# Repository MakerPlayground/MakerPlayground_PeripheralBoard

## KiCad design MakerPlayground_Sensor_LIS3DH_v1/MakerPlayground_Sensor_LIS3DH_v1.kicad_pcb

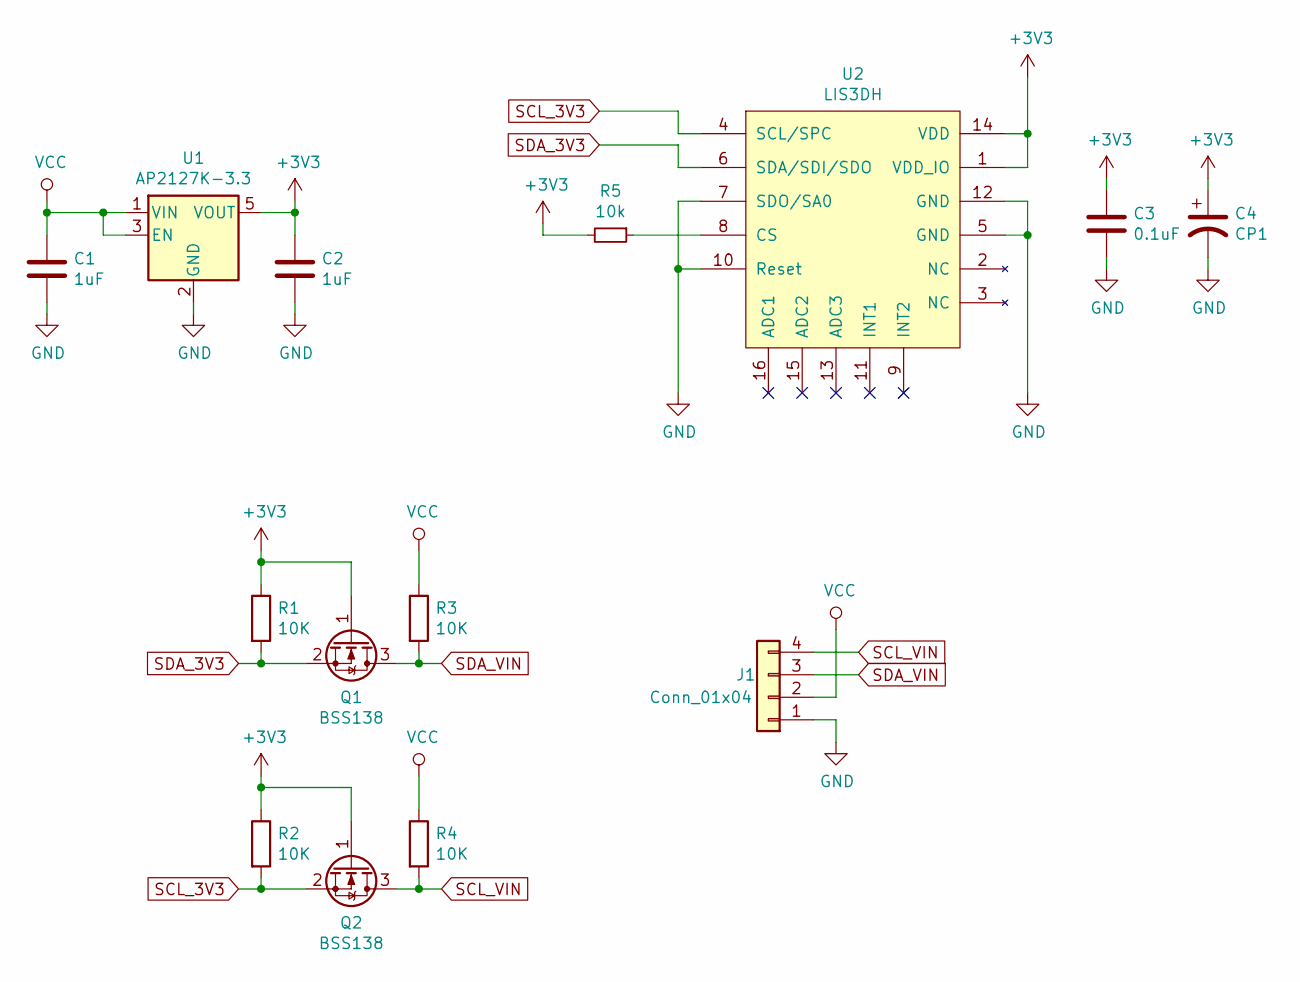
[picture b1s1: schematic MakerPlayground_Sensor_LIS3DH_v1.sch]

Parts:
C1, C2: 1uF; C_0603_1608Metric
C3: 0.1uF; C_0603_1608Metric
C4: CP1; CP_EIA-3216-12_Kemet-S
J1: Conn_01x04; JST_PH_S4B-PH-SM4-TB_1x04-1MP_P2.00mm_Horizontal
Q1, Q2: BSS138; SOT-23
R1, R2, R3, R4: 10K; R_0603_1608Metric
R5: 10k; R_0603_1608Metric
U1: AP2127K-3.3; SOT-23-5
U2: LIS3DH

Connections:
+3V3: C2.1, C3.1, C4.1, Q1.1 (G), Q2.1 (G), R1.1, R2.1, R5.2, U1.5 (VOUT), U2.1 (VDD_IO), U2.14 (VDD)
GND: C1.2, C2.2, C3.2, C4.2, J1.1, U1.2 (GND), U2.5 (GND), U2.7 (SDO/SA0), U2.10 (Reset), U2.12 (GND)
unnamed: R5.1, U2.8 (CS)
SCL_3V3: Q2.2 (S), R2.2, U2.4 (SCL/SPC)
SCL_VIN: J1.4, Q2.3 (D), R4.2
SDA_3V3: Q1.2 (S), R1.2, U2.6 (SDA/SDI/SDO)
SDA_VIN: J1.3, Q1.3 (D), R3.2
VCC: C1.1, J1.2, R3.1, R4.1, U1.1 (VIN), U1.3 (EN)

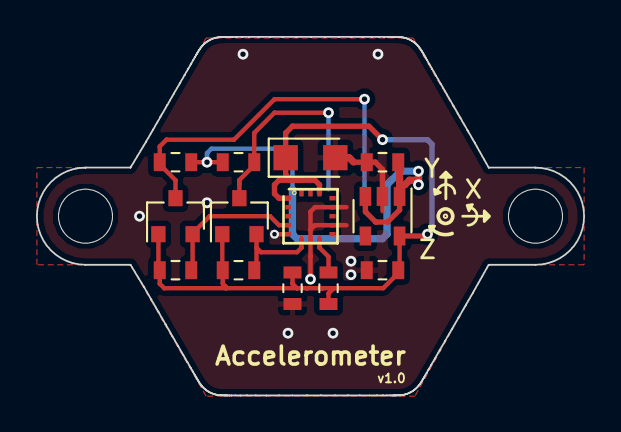
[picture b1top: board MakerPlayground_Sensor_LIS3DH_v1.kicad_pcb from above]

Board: 2 copper layers, 30.4 x 19.9 mm, 14 parts (1 on the bottom side), 8 nets.

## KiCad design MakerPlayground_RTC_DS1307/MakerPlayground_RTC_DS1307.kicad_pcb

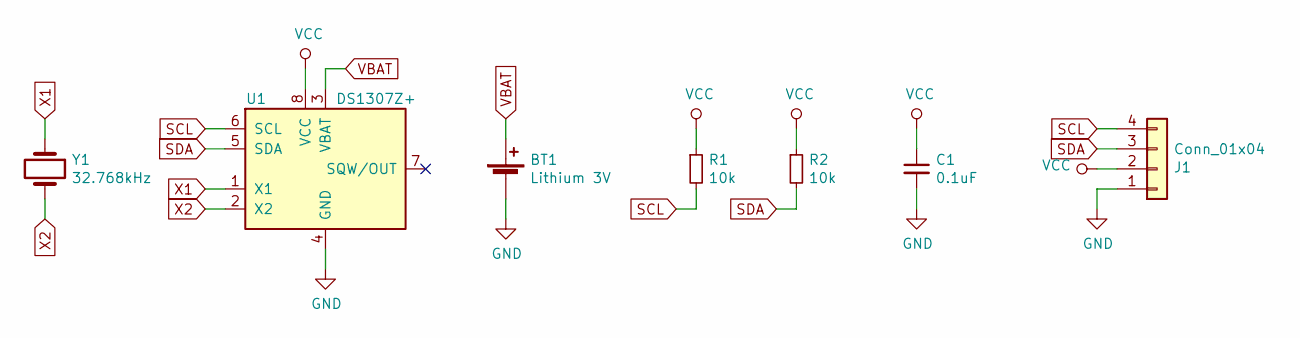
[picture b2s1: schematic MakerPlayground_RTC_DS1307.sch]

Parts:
BT1: Lithium 3V; BL-25T-GLT
C1: 0.1uF; C_0603_1608Metric
J1: Conn_01x04; JST_PH_S4B-PH-K_1x04_P2.00mm_Horizontal
R1, R2: 10k; R_0603_1608Metric
U1: DS1307Z+; SOIC-8_3.9x4.9mm_P1.27mm
Y1: 32.768kHz; Crystal_SMD_3215-2Pin_3.2x1.5mm

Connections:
GND: BT1.2 (-), C1.2, J1.1, U1.4 (GND)
SCL: J1.4, R1.2, U1.6 (SCL)
SDA: J1.3, R2.2, U1.5 (SDA)
VBAT: BT1.1 (+), U1.3 (VBAT)
VCC: C1.1, J1.2, R1.1, R2.1, U1.8 (VCC)
X1: U1.1 (X1), Y1.1
X2: U1.2 (X2), Y1.2

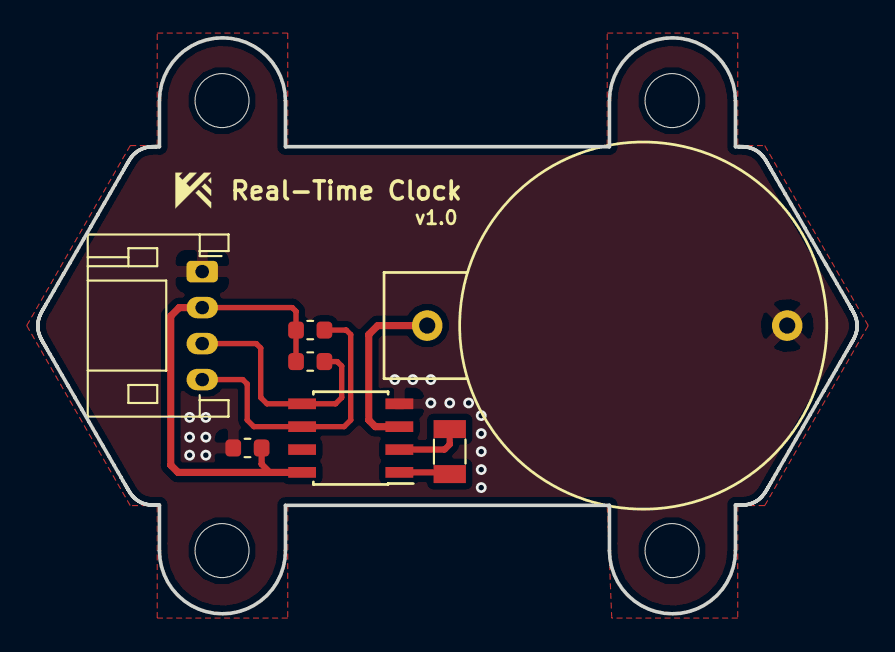
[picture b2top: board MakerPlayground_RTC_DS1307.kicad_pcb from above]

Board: 2 copper layers, 45.5 x 32.0 mm, 7 parts (0 on the bottom side), 7 nets.

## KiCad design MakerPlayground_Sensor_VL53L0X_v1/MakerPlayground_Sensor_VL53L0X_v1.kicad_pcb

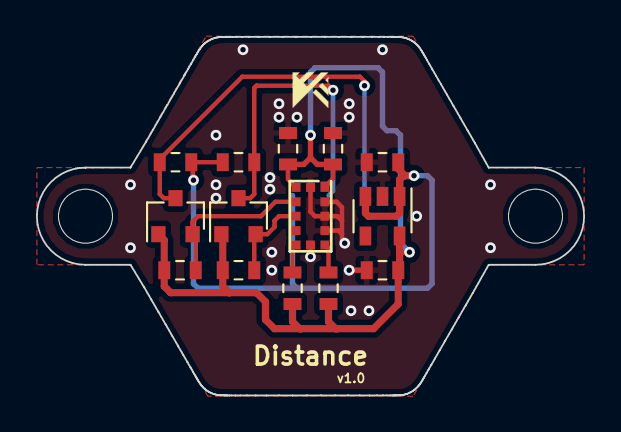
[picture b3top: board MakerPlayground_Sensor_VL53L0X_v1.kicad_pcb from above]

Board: 2 copper layers, 30.4 x 19.9 mm, 15 parts (1 on the bottom side), 9 nets.

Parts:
C1: 4.7uF; C_0603_1608Metric
C2: 0.1uF; C_0603_1608Metric
C4, C5: 1uF; C_0603_1608Metric
J1: Connector; JST_PH_S4B-PH-SM4-TB_1x04-1MP_P2.00mm_Horizontal
Q1, Q2: BSS138; SOT-23
R1, R2, R3, R4, R5, R6: 10k; R_0603_1608Metric
U1: VL53L0X
U2: AP2127K-3.3; SOT-23-5

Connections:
+3V3: C1.1, C2.1, C5.1, Q1.1, Q2.1, R1.1, R3.2, R5.2, R6.1, U1.1, U1.11, U2.5
GND: C1.2, C2.2, C4.2, C5.2, J1.1, U1.2, U1.3, U1.4, U1.6, U1.12, U2.2
unnamed: R1.2, U1.7
unnamed: R6.2, U1.5
SCL: J1.4, Q2.3, R4.1
SCL_S: Q2.2, R5.1, U1.10
SDA: J1.3, Q1.3, R2.1
SDA_S: Q1.2, R3.1, U1.9
VCC: C4.1, J1.2, R2.2, R4.2, U2.1, U2.3

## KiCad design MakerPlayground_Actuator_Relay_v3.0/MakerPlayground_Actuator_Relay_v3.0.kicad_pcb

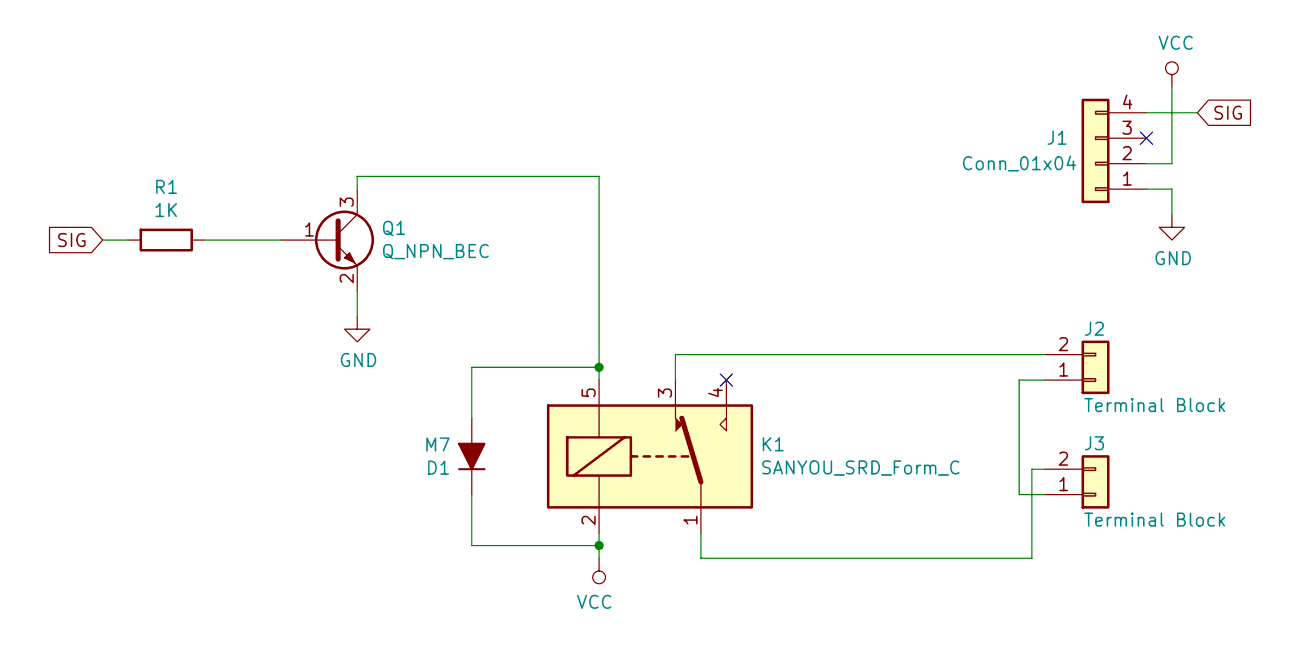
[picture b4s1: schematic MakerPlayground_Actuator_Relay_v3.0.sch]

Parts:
D1: M7; D_SMA
J1: Conn_01x04; JST_PH_S4B-PH-K_1x04_P2.00mm_Horizontal
J2, J3: Terminal Block; TerminalBlock_Dinkle_ED350V_1x02_P3.50mm_Horizontal
K1: SANYOU_SRD_Form_C; Relay_SPDT_SANYOU_SRD_Series_Form_C
Q1: Q_NPN_BEC; SOT-23
R1: 1K; R_0603_1608Metric

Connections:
GND: J1.1, Q1.2 (E)
unnamed: D1.2 (A), K1.5, Q1.3 (C)
unnamed: J2.1, J3.1
unnamed: J2.2, K1.3
unnamed: J3.2, K1.1
unnamed: Q1.1 (B), R1.1
SIG: J1.4, R1.2
VCC: D1.1 (K), J1.2, K1.2

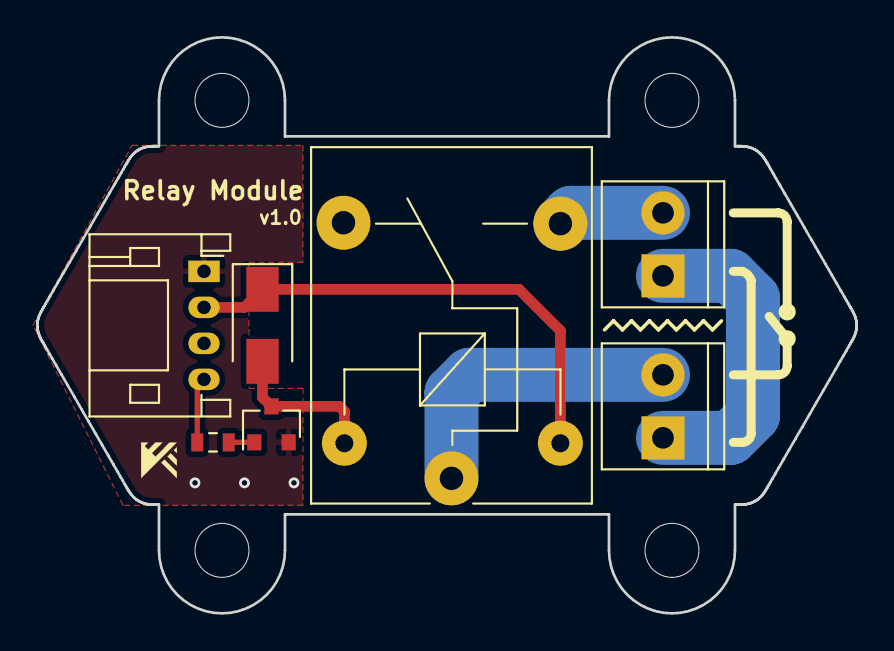
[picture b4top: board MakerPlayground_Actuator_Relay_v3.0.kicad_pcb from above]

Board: 2 copper layers, 45.5 x 32.0 mm, 7 parts (0 on the bottom side), 8 nets.

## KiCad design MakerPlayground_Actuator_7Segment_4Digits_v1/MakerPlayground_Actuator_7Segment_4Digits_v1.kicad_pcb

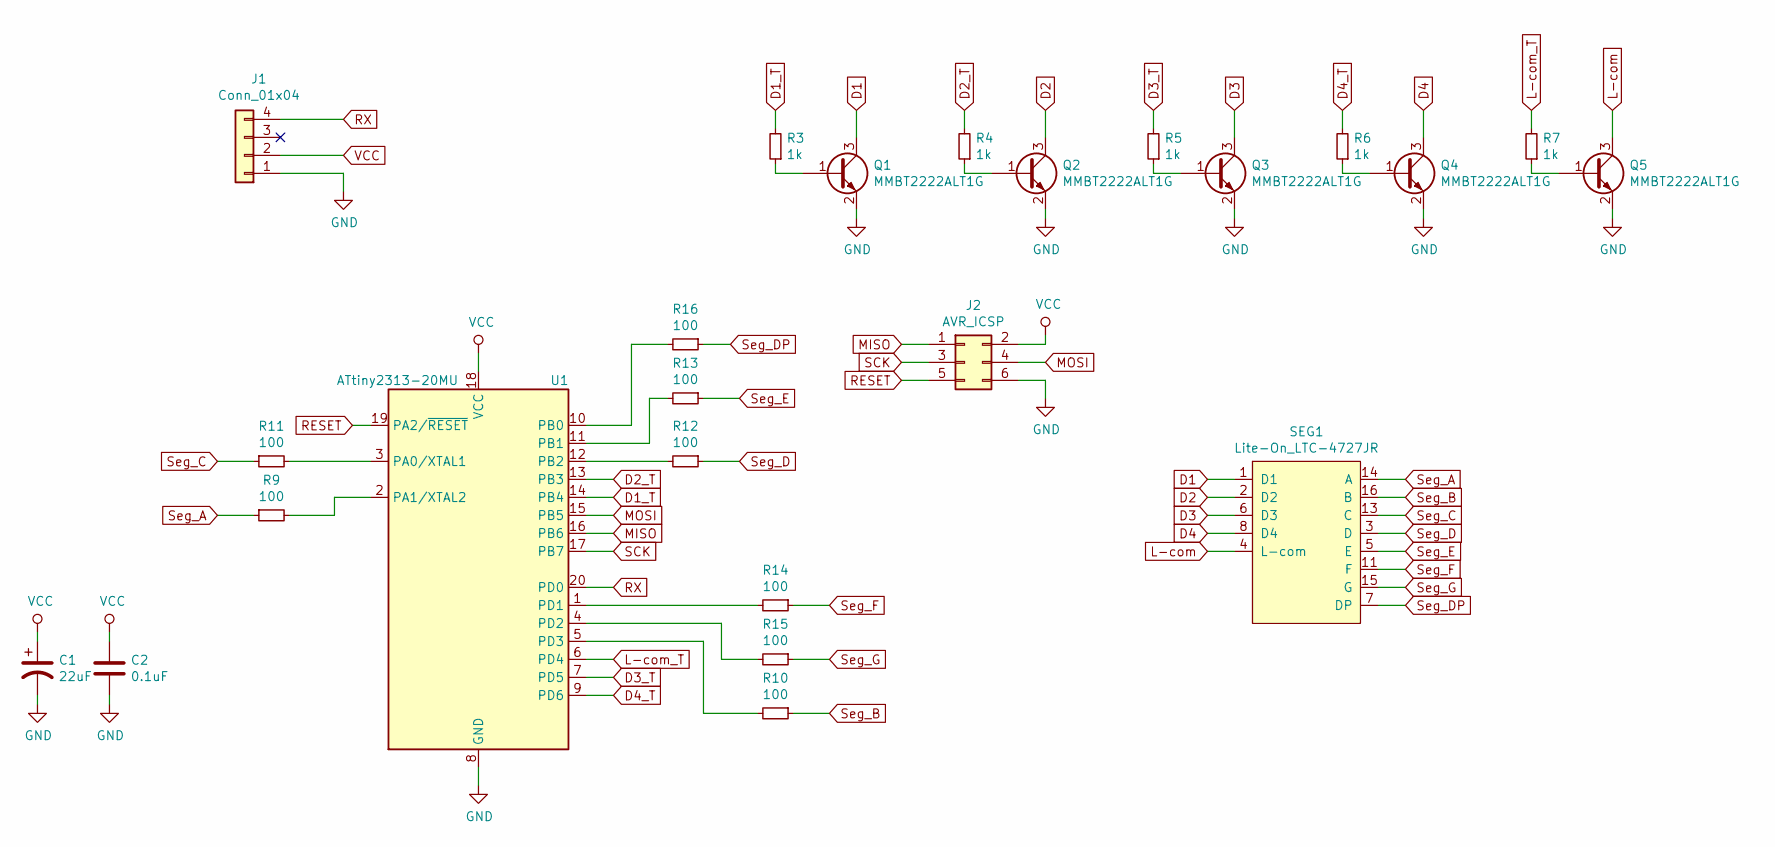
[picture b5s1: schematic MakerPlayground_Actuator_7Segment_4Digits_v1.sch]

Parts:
C1: 22uF; CP_EIA-3216-12_Kemet-S
C2: 0.1uF; C_0603_1608Metric
J1: Conn_01x04; JST_PH_S4B-PH-SM4-TB_1x04-1MP_P2.00mm_Horizontal
J2: AVR_ICSP; PinHeader_2x03_P2.54mm_Vertical
Q1, Q2, Q3, Q4, Q5: MMBT2222ALT1G; SOT-23
R3, R4, R5, R6, R7: 1k; R_0603_1608Metric
R9, R10, R11, R12, R13, R14, R15, R16: 100; R_0603_1608Metric
SEG1: Lite-On_LTC-4727JR; LTC-4727JR
U1: ATtiny2313-20MU; QFN-20-1EP_4x4mm_P0.5mm_EP2.5x2.5mm

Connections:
D1: Q1.3 (C), SEG1.1 (D1)
D1_T: R3.2, U1.14 (PB4)
D2: Q2.3 (C), SEG1.2 (D2)
D2_T: R4.2, U1.13 (PB3)
D3: Q3.3 (C), SEG1.6 (D3)
D3_T: R5.2, U1.7 (PD5)
D4: Q4.3 (C), SEG1.8 (D4)
D4_T: R6.2, U1.9 (PD6)
GND: C1.2, C2.2, J1.1, J2.6, Q1.2 (E), Q2.2 (E), Q3.2 (E), Q4.2 (E), Q5.2 (E), U1.8 (GND), U1.21 (GND)
L-com: Q5.3 (C), SEG1.4 (L-com)
L-com_T: R7.2, U1.6 (PD4)
MISO: J2.1, U1.16 (PB6)
MOSI: J2.4, U1.15 (PB5)
unnamed: Q1.1 (B), R3.1
unnamed: Q2.1 (B), R4.1
unnamed: Q3.1 (B), R5.1
unnamed: Q4.1 (B), R6.1
unnamed: Q5.1 (B), R7.1
unnamed: R9.2, U1.2 (PA1/XTAL2)
unnamed: R10.2, U1.5 (PD3)
unnamed: R11.2, U1.3 (PA0/XTAL1)
unnamed: R12.2, U1.12 (PB2)
unnamed: R13.2, U1.11 (PB1)
unnamed: R14.2, U1.1 (PD1)
unnamed: R15.2, U1.4 (PD2)
unnamed: R16.2, U1.10 (PB0)
RESET: J2.5, U1.19 (PA2/~RESET)
RX: J1.4, U1.20 (PD0)
SCK: J2.3, U1.17 (PB7)
Seg_A: R9.1, SEG1.14 (A)
Seg_B: R10.1, SEG1.16 (B)
Seg_C: R11.1, SEG1.13 (C)
Seg_D: R12.1, SEG1.3 (D)
Seg_DP: R16.1, SEG1.7 (DP)
Seg_E: R13.1, SEG1.5 (E)
Seg_F: R14.1, SEG1.11 (F)
Seg_G: R15.1, SEG1.15 (G)
VCC: C1.1, C2.1, J1.2, J2.2, U1.18 (VCC)

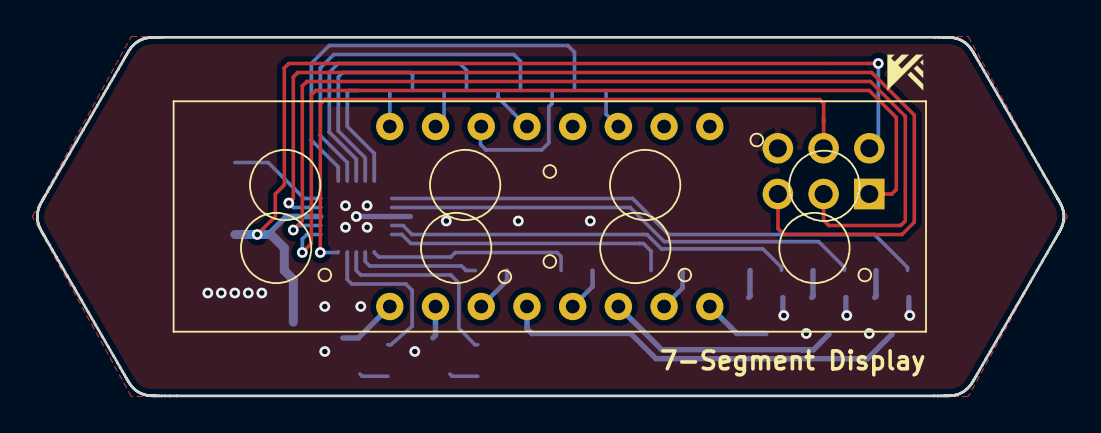
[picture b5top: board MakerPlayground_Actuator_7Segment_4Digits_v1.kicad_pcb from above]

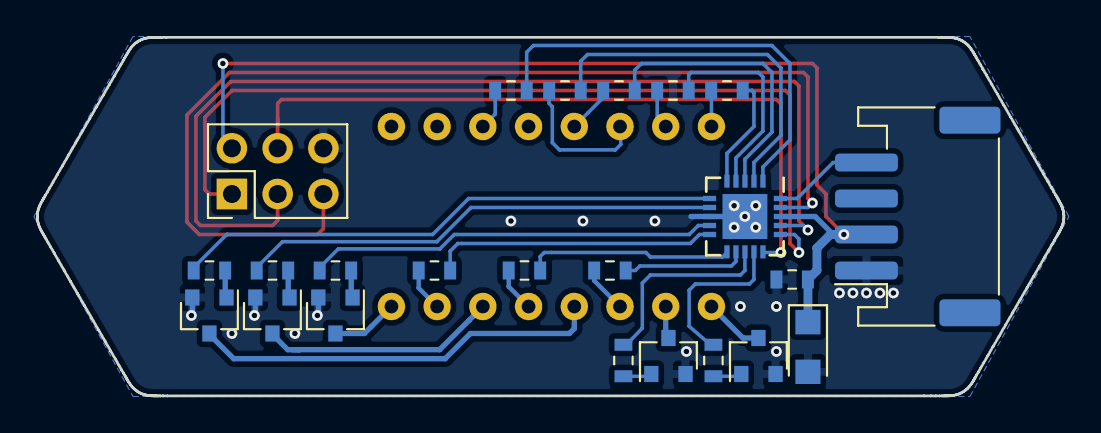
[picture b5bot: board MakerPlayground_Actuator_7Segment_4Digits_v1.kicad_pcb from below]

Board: 2 copper layers, 57.0 x 19.9 mm, 24 parts (23 on the bottom side), 38 nets.

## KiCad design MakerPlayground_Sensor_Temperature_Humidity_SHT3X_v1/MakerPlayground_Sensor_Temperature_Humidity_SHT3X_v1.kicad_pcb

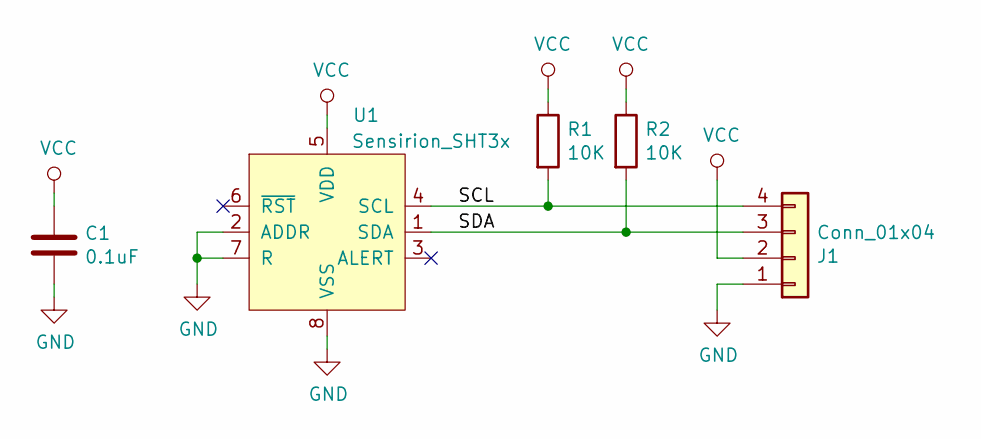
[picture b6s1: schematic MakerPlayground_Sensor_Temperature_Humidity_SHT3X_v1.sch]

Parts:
C1: 0.1uF; C_0603_1608Metric
J1: Conn_01x04; JST_PH_S4B-PH-SM4-TB_1x04-1MP_P2.00mm_Horizontal
R1, R2: 10K; R_0603_1608Metric
U1: Sensirion_SHT3x

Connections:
/SCL: J1.4, R1.2, U1.4 (SCL)
/SDA: J1.3, R2.2, U1.1 (SDA)
GND: C1.2, J1.1, U1.2 (ADDR), U1.7 (R), U1.8 (VSS), U1.9 (PAD)
VCC: C1.1, J1.2, R1.1, R2.1, U1.5 (VDD)

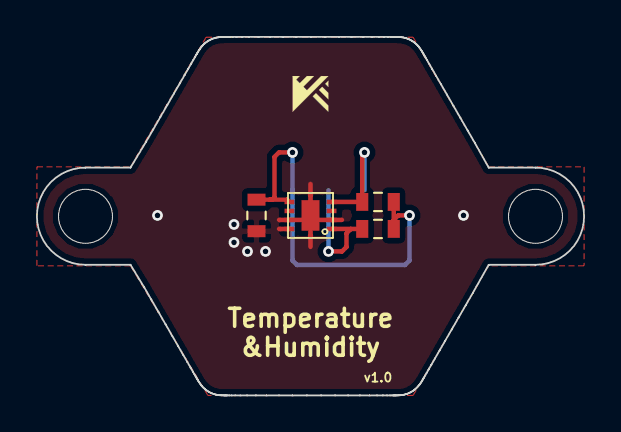
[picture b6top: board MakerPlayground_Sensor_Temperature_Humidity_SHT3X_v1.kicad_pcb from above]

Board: 2 copper layers, 30.4 x 19.9 mm, 5 parts (1 on the bottom side), 4 nets.

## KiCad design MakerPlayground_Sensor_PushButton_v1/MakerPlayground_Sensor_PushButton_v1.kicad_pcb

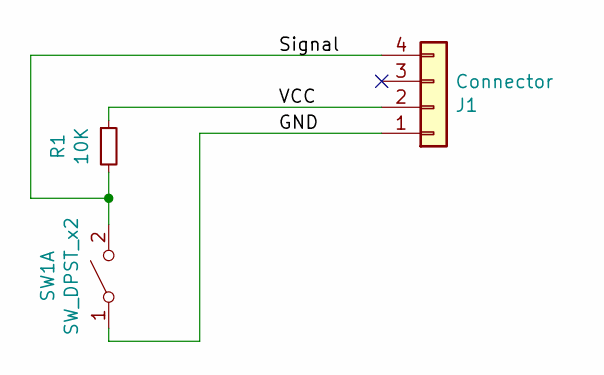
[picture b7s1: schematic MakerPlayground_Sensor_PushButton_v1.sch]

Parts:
J1: Connector; JST_PH_S4B-PH-SM4-TB_1x04-1MP_P2.00mm_Horizontal
R1: 10K; R_0603_1608Metric_Pad0.84x1.00mm_HandSolder
SW1: SW_DPST_x2; SW_SPST_B3S-1000

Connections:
/GND: J1.1, SW1.1 (A)
/Signal: J1.4, R1.2, SW1.2 (B)
/VCC: J1.2, R1.1

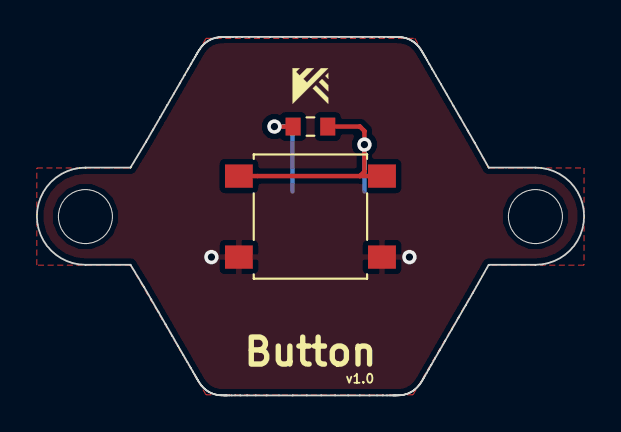
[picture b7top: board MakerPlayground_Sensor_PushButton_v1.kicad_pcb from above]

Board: 2 copper layers, 30.4 x 19.9 mm, 3 parts (1 on the bottom side), 3 nets.

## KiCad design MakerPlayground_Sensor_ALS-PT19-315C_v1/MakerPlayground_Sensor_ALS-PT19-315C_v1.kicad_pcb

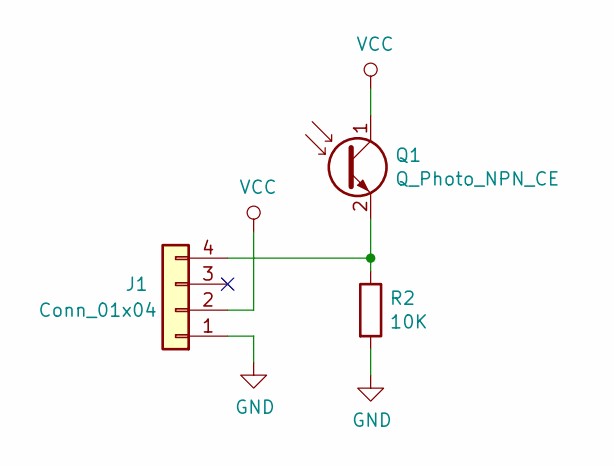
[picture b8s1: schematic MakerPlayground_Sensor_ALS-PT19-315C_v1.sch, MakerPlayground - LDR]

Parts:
J1: Conn_01x04; JST_PH_S4B-PH-SM4-TB_1x04-1MP_P2.00mm_Horizontal
Q1: Q_Photo_NPN_CE; R_0603_1608Metric
R2: 10K; R_0603_1608Metric

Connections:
GND: J1.1, R2.2
unnamed: J1.4, Q1.2 (E), R2.1
VCC: J1.2, Q1.1 (C)

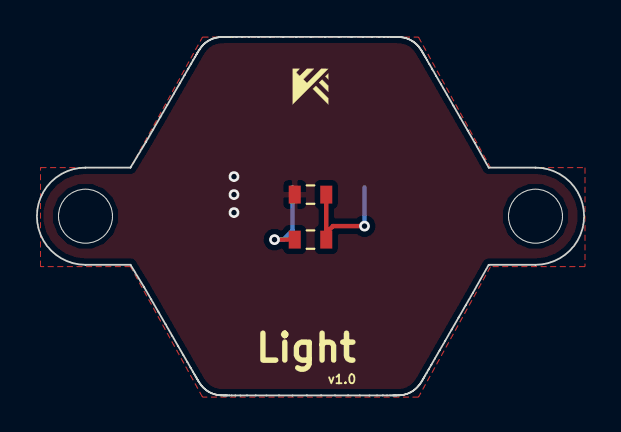
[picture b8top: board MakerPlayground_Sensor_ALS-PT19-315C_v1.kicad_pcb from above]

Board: 2 copper layers, 30.4 x 19.9 mm, 3 parts (1 on the bottom side), 3 nets.

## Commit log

2019-02-24 ~ 1st commit to development branch ~
2019-02-24 Add temp mounthing hole to RGB LED
2019-02-26 RGB LED mounting hole barrier size experiment.
2019-02-26 Add Single HEX shape edge cut design.
2019-02-26 Finalize RGB LED SK9822 PCB design.
2019-02-26 Fix Single HEX edge cut DXF file.
2019-02-26 Minor fix H-bridge Motor driver.
2019-02-26 Fix LED-SMD PCB design edge cut and mounting hole.
2019-02-26 Fix MP Light sensor mounting hole & connector.
2019-02-26 Fix MP Light sensor silk screen.
2019-02-26 Fix Temperature sensor PCB design edge cut and mounting hole.
2019-02-26 Fix Accel-only sensor, add mounting hole.
2019-02-26 Add mounting hole to LSM6DS3 (Accel + Gyro) sensor.
2019-02-26 Fix schematic issue.
2019-02-26 Fix POT symbol in schematic & SMD connector footprint change + mounting hole.
2019-02-26 Add mounting hole & change to SMD connector.
2019-02-26 Add mounting hole.
2019-02-26 Single HEX design; Lock mounting hole footprint & review mounting hole position.
2019-02-26 Under editing mounting hole.
2019-02-27 Add Rriple HEX edge cut DXF file.
2019-02-27 Update Relay board mounting hole design.
2019-02-27 Update Relay PCB design & verification needed.
2019-02-27 Complete editing edge cut & adding mouning hole.
2019-02-27 Edge cut under renovation.
2019-02-28 Fix wiring error.
2019-02-28 Add piezo buzzer edge cut template.
2019-02-28 Design complete.
2019-02-28 Complete design.
2019-04-04 First commit, in reviewing process.
2019-04-07 Finalize GND plane filling.
2019-04-07 Fix missing MP 2x2 logo.
2019-04-07 Fix missing GND plane.
2019-04-07 Improve GND PTH, GND spreading area. Ready to fab.
2019-04-10 Add OLED display PCB design. Working on it, not complete.
2019-04-10 Doing to job ngai. Still not complete jaaa.
2019-04-12 Battery holder footprint incomplete.
2019-04-12 Complete
2019-04-18 Update EdgeCut shape & Add mounting hole.
2019-04-19 Fix missing capacitor description. Complete.
